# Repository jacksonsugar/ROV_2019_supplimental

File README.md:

# ROV_2019_supplimental
Documents and CAD for the 2019 ROV

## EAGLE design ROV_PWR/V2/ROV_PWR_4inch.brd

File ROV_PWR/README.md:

Two types here. The vicor product on the 4 inch failed and had to spec a new part. Never printed number 2.

Suggest making new one all together.

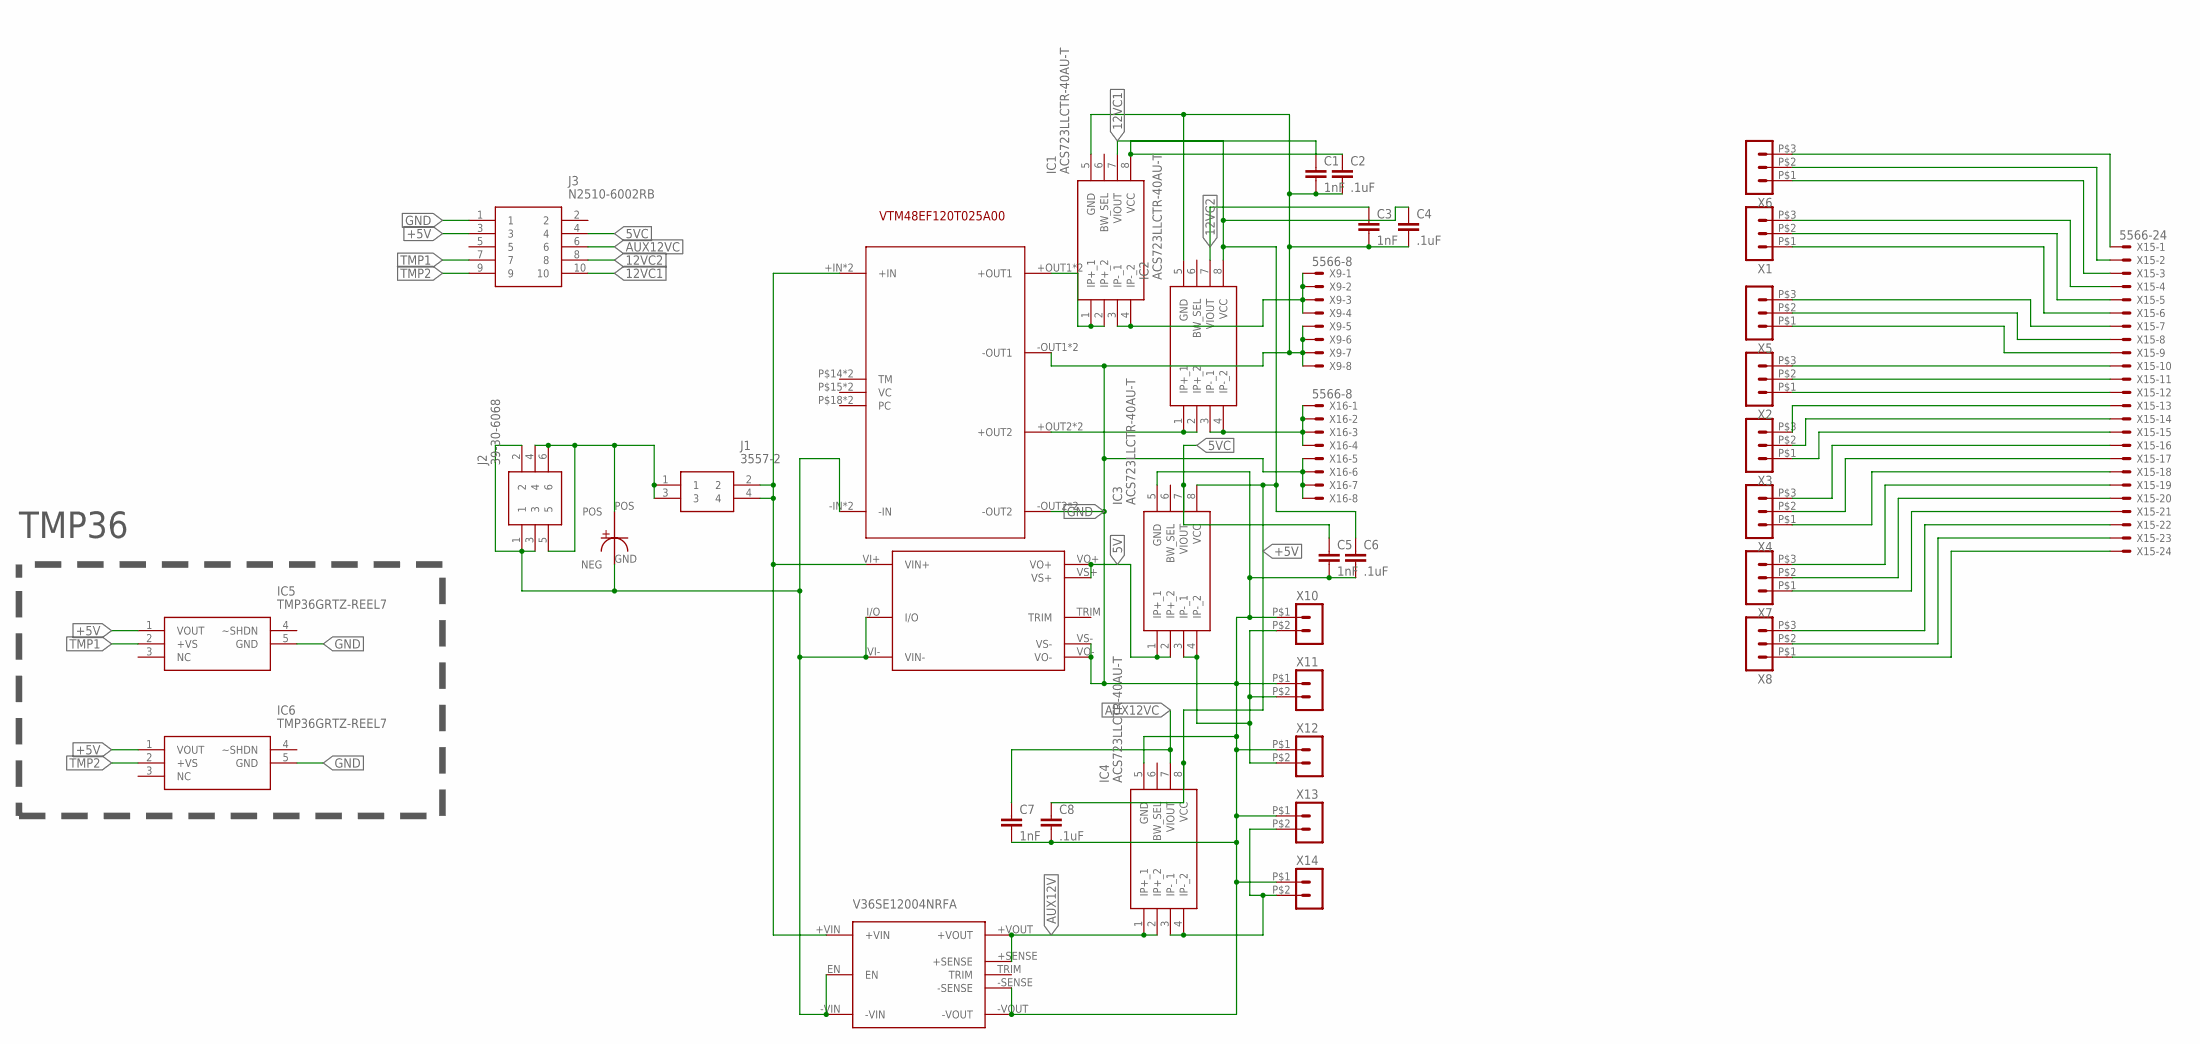
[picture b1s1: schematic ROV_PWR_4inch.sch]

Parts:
C1, C3, C5, C7: 1nF; C0402
C2, C4, C6, C8: .1uF; C0402
IC1, IC2, IC3, IC4: ACS723LLCTR-40AU-T; SOT127P600X175-8N
IC5, IC6: TMP36GRTZ-REEL7; SOT95P280X145-5N
J1: 3557-2
J2: 39-30-6068; 39306068
J3: N2510-6002RB; SHDR10W64P254_2X5_2002X859X100
U$1: VTM48EF120T025A00
U$2: KHHD006A0A41Z
U$3: V36SE12004NRFA
U$4: UBY1V222MHL
X1, X2, X3, X4, X5, X6, X7, X8: HEADER_POS3_43650-0315; 43650-0315
X9, X16: 5566-8
X10, X11, X12, X13, X14: HEADER_POS2_44914-0201; 44914-0201
X15: 5566-24

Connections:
5V: IC3.1 (IP+_1), IC3.2 (IP+_2), U$2.VO+, U$2.VS+
5VC: C5.1, IC3.7 (VIOUT), J3.4
12VC1: C1.1, IC1.7 (VIOUT), J3.10
12VC2: C3.1, IC2.7 (VIOUT), J3.8
+5V: C2.1, C4.1, C6.1, C8.1, IC1.8 (VCC), IC2.8 (VCC), IC3.8 (VCC), IC4.8 (VCC), IC5.1 (VOUT), IC6.1 (VOUT), J3.3
AUX12V: IC4.1 (IP+_1), IC4.2 (IP+_2), U$3.+SENSE, U$3.+VOUT
AUX12VC: C7.1, IC4.7 (VIOUT), J3.6
GND: C1.2, C2.2, C3.2, C4.2, C5.2, C6.2, C7.2, C8.2, IC1.5 (GND), IC2.5 (GND), IC3.5 (GND), IC4.5 (GND), IC5.5 (GND), IC6.5 (GND), J3.1, U$1.-OUT1, U$1.-OUT2, U$1.P$1 (-OUT1), U$1.P$4 (-OUT2), U$2.VO-, U$2.VS-, U$3.-SENSE, U$3.-VOUT, X9.5, X9.6, X9.7, X9.8, X10.P$1 (1), X11.P$1 (1), X12.P$1 (1), X13.P$1 (1), X14.P$1 (1), X16.5, X16.6, X16.7, X16.8
unnamed: X6.P$3 (3), X15.1
unnamed: X6.P$2 (2), X15.2
unnamed: X6.P$1 (1), X15.3
unnamed: X1.P$3 (3), X15.4
unnamed: X1.P$2 (2), X15.5
unnamed: X1.P$1 (1), X15.6
unnamed: X5.P$3 (3), X15.7
unnamed: X5.P$2 (2), X15.8
unnamed: X5.P$1 (1), X15.9
unnamed: X2.P$3 (3), X15.10
unnamed: X2.P$2 (2), X15.11
unnamed: X2.P$1 (1), X15.12
unnamed: X3.P$3 (3), X15.13
unnamed: X3.P$2 (2), X15.14
unnamed: X3.P$1 (1), X15.15
unnamed: X4.P$3 (3), X15.16
unnamed: X4.P$2 (2), X15.17
unnamed: X4.P$1 (1), X15.18
unnamed: X7.P$3 (3), X15.19
unnamed: X7.P$2 (2), X15.20
unnamed: X7.P$1 (1), X15.21
unnamed: X8.P$3 (3), X15.22
unnamed: X8.P$2 (2), X15.23
unnamed: X8.P$1 (1), X15.24
unnamed: J1.2, J1.4, U$1.+IN, U$1.P$9 (+IN), U$2.VI+ (VIN+), U$3.+VIN
unnamed: IC1.1 (IP+_1), IC1.2 (IP+_2), U$1.+OUT1, U$1.P$3 (+OUT1)
unnamed: J2.1, J2.2, J2.3, U$1.-IN, U$1.P$11 (-IN), U$2.I/O, U$2.VI- (VIN-), U$3.-VIN, U$3.EN, U$4.GND (NEG)
unnamed: J1.1, J1.3, J2.4, J2.5, J2.6, U$4.POS
unnamed: IC3.3 (IP-_1), IC3.4 (IP-_2), X10.P$2 (2), X11.P$2 (2), X12.P$2 (2)
unnamed: IC4.3 (IP-_1), IC4.4 (IP-_2), X13.P$2 (2), X14.P$2 (2)
unnamed: IC2.1 (IP+_1), IC2.2 (IP+_2), U$1.+OUT2, U$1.P$2 (+OUT2)
unnamed: IC2.3 (IP-_1), IC2.4 (IP-_2), X16.1, X16.2, X16.3, X16.4
unnamed: IC1.3 (IP-_1), IC1.4 (IP-_2), X9.1, X9.2, X9.3, X9.4
TMP1: IC5.2 (+VS), J3.7
TMP2: IC6.2 (+VS), J3.9

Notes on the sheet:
TMP36

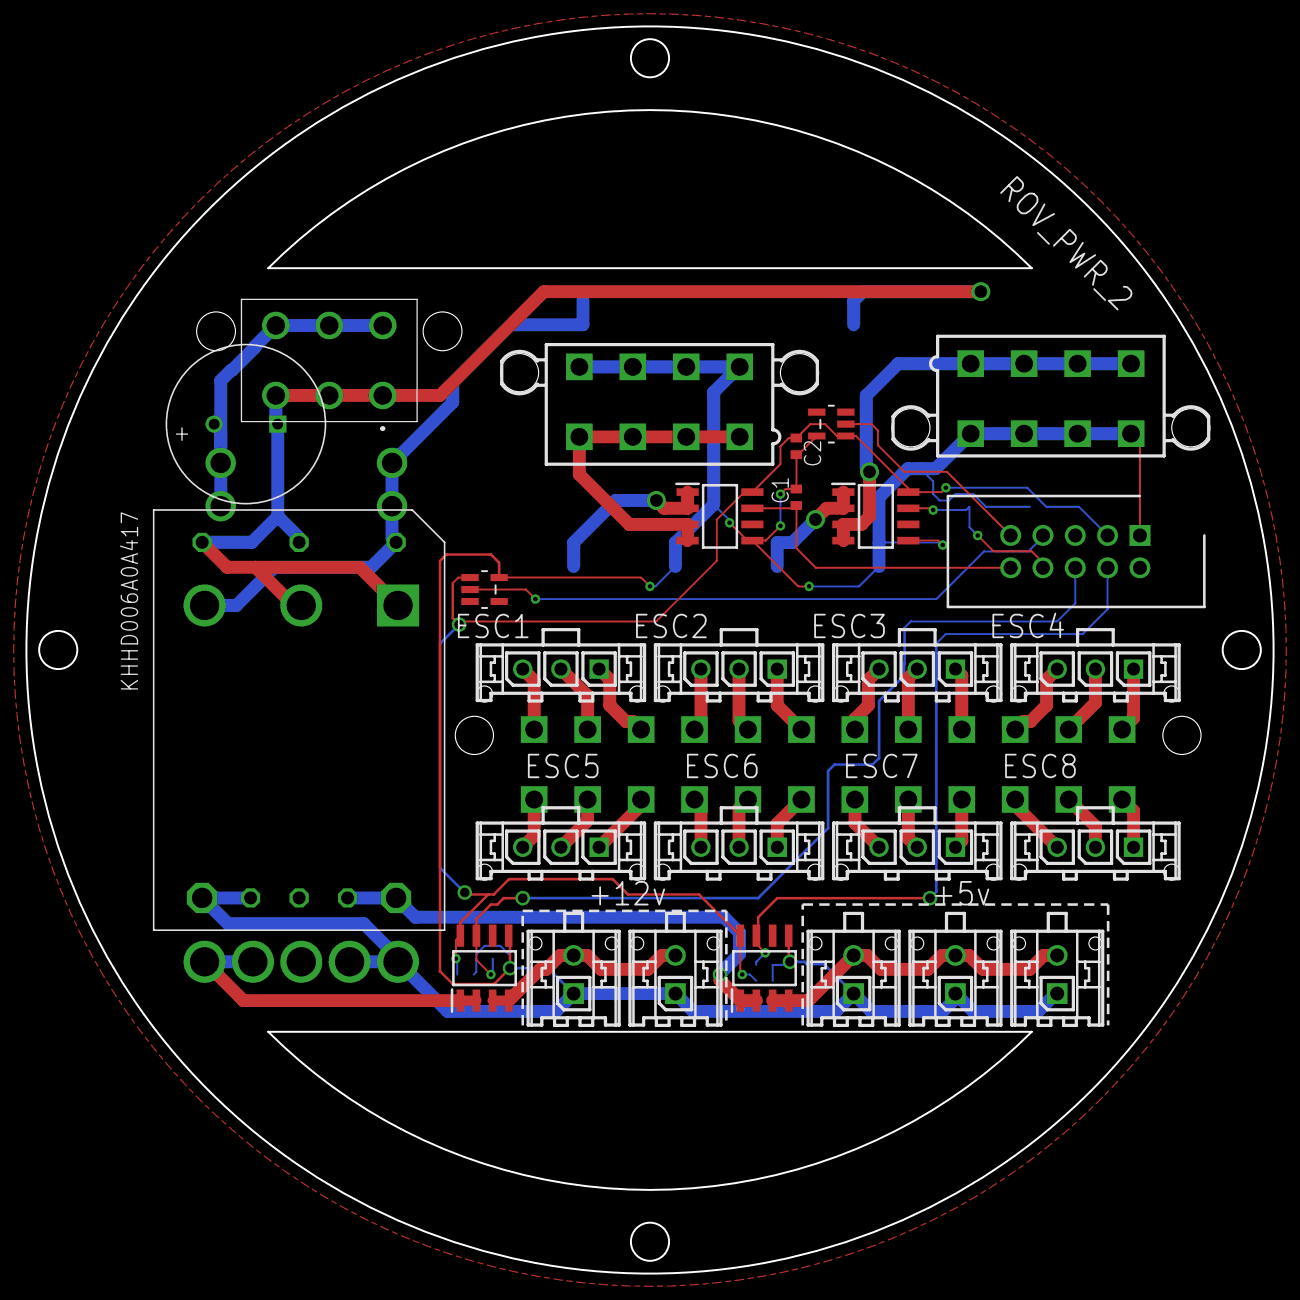
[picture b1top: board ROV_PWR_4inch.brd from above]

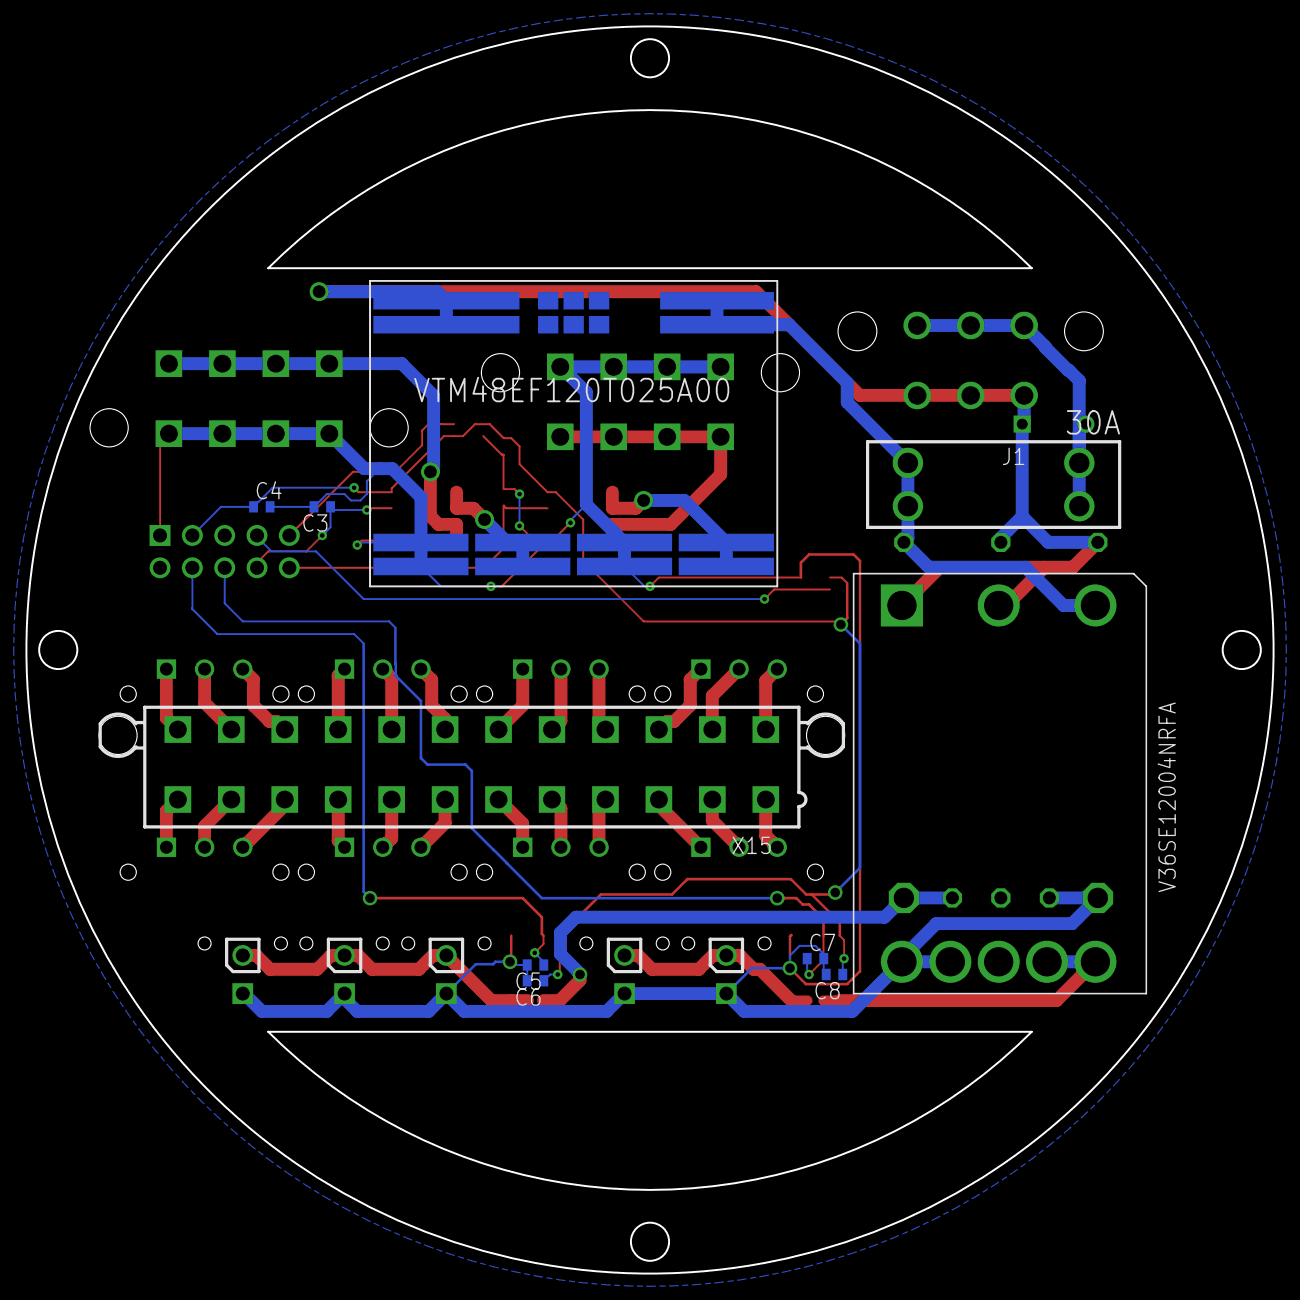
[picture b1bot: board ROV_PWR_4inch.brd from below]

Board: 2 copper layers, 98.0 x 98.0 mm, 37 parts (10 on the bottom side), 43 nets.

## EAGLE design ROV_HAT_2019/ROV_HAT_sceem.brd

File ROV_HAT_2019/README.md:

Designed for the NanoPi M4. Locatoin of the serial pins are propriatary.

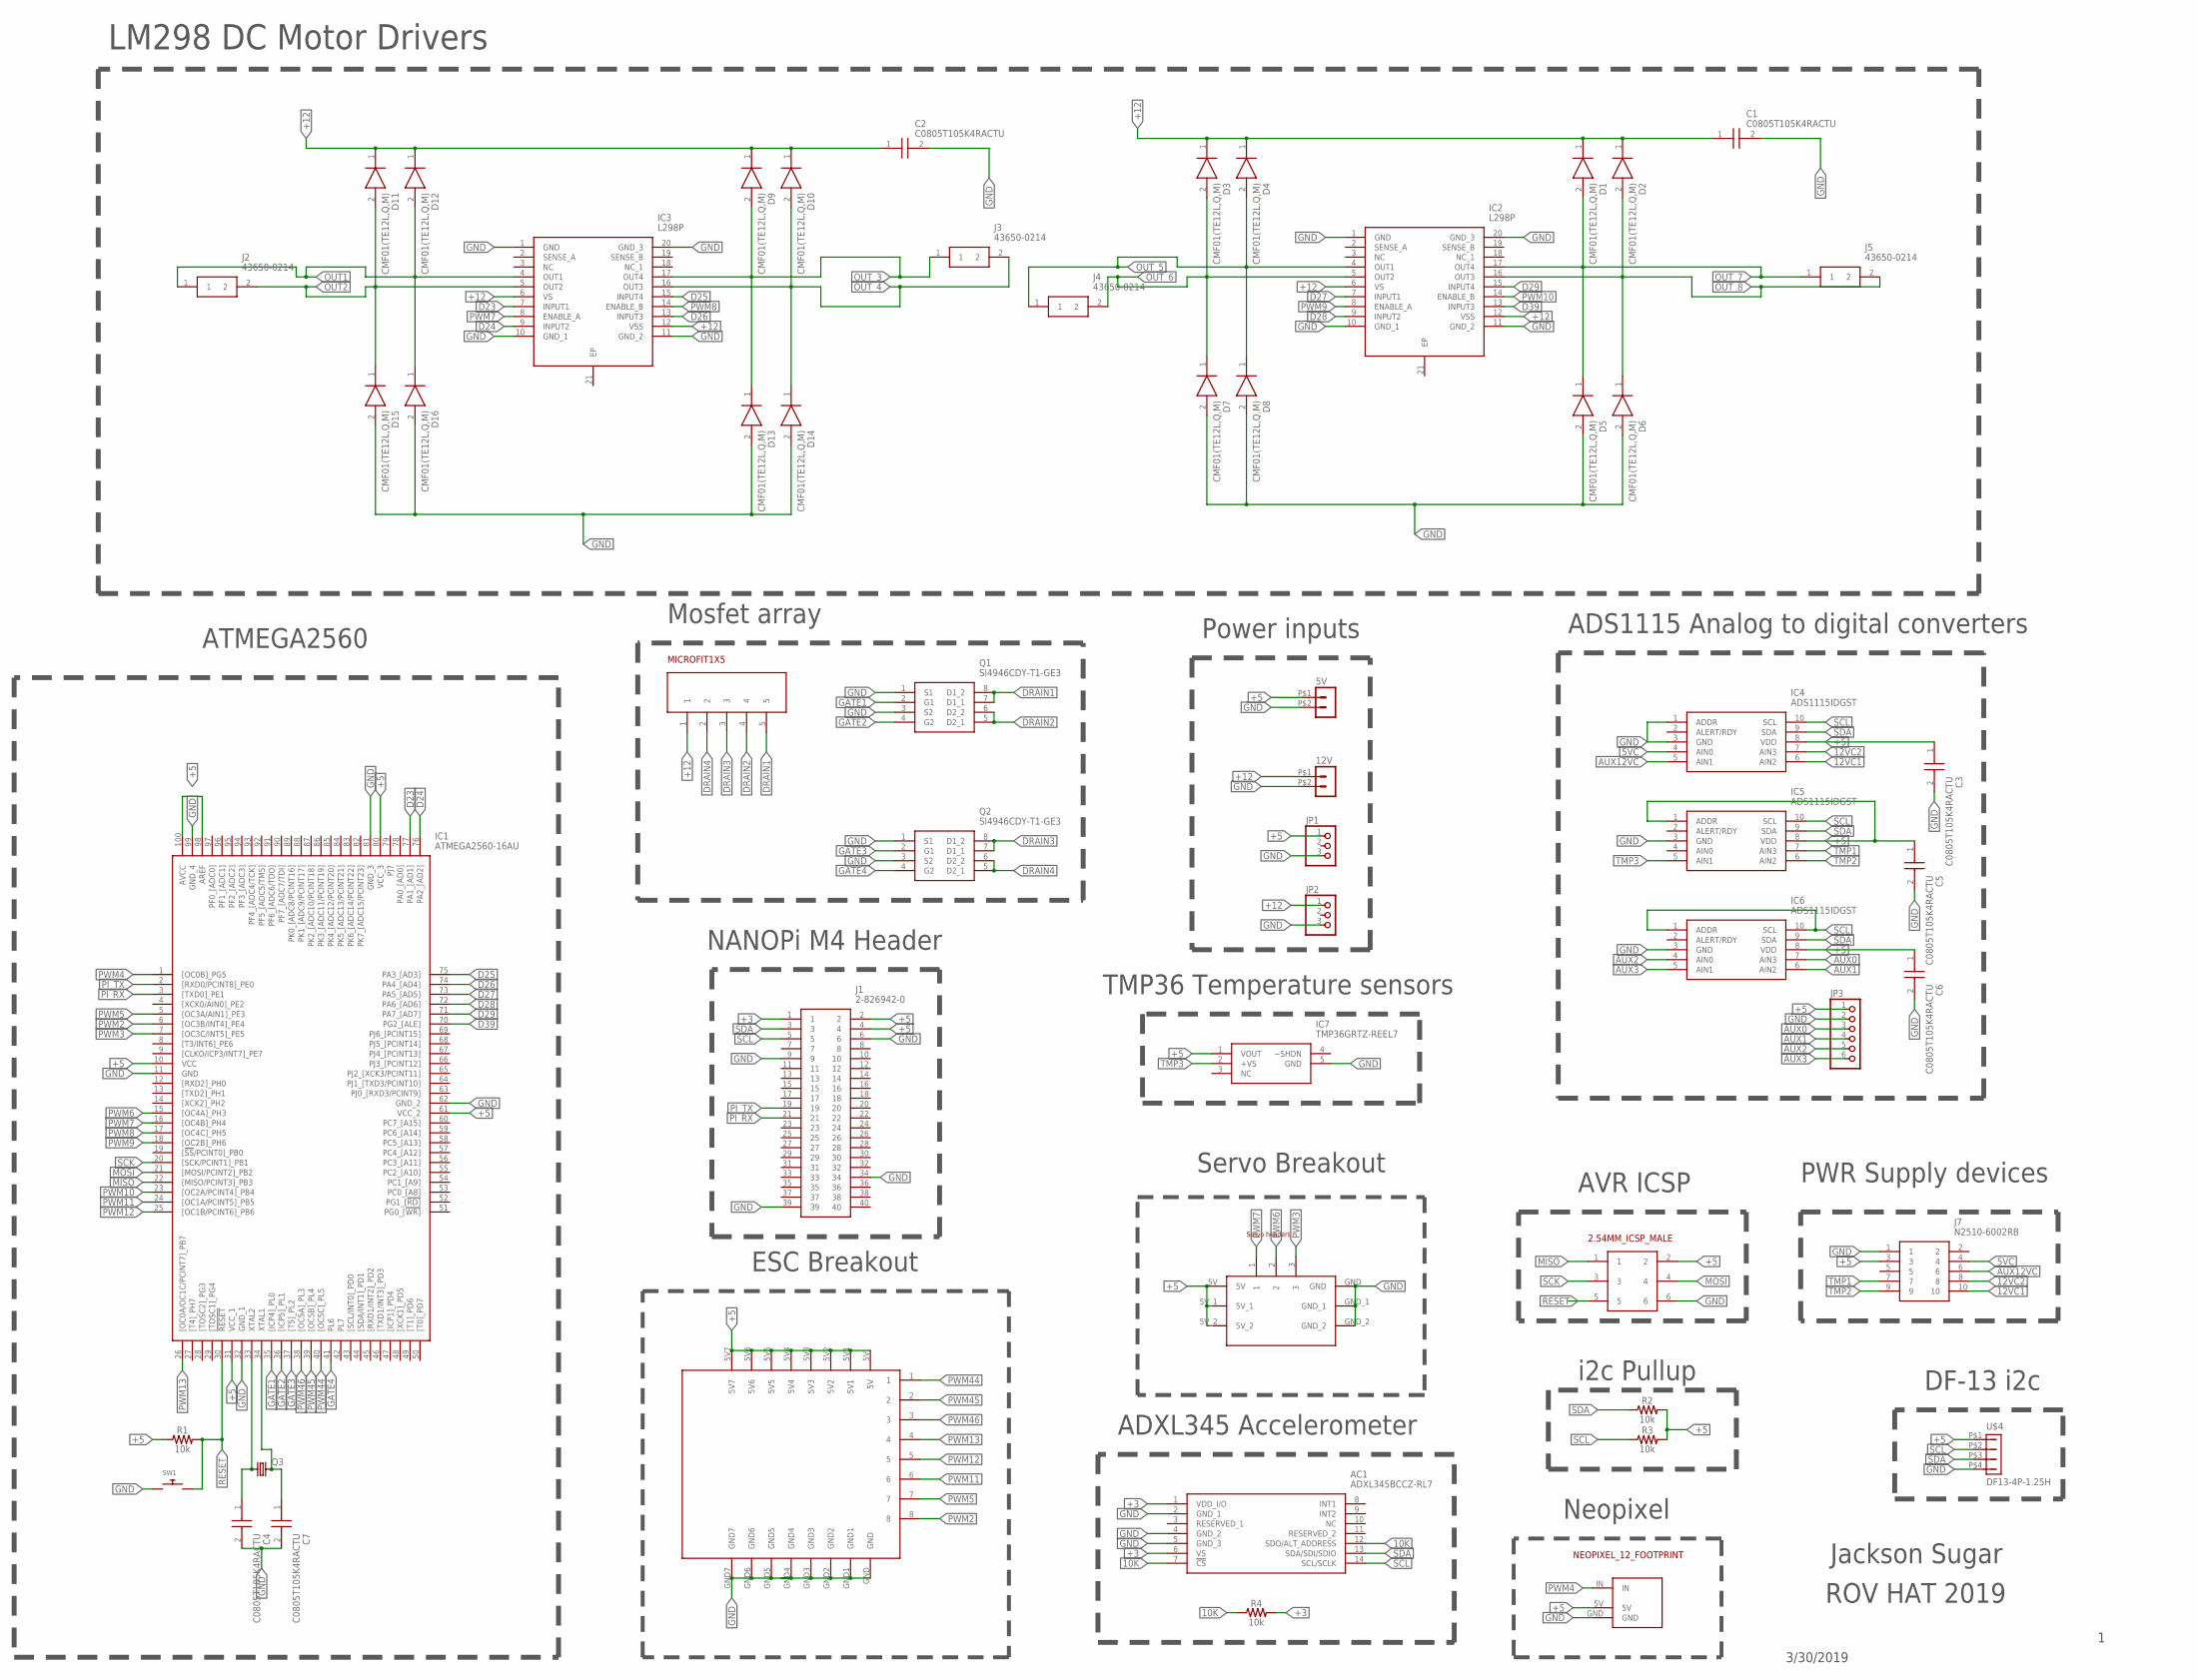
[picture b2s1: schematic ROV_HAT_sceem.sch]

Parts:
5V: HEADER_POS2_43045-0200; 43045-0200
12V: HEADER_POS2_43650-0200; 43650-0200
AC1: ADXL345BCCZ-RL7; CC-14-1
C1, C2, C3, C4, C5, C6, C7: C0805T105K4RACTU; CAPC2012X100N
D1, D2, D3, D4, D5, D6, D7, D8, D9, D10, D11, D12, D13, D14, D15, D16: CMF01(TE12L,Q,M); SODFL4724X108N
IC1: ATMEGA2560-16AU; QFP50P1600X1600X120-100N
IC2, IC3: L298P; SOIC127P1420X360-21N
IC4, IC5, IC6: ADS1115IDGST; SOP50P490X110-10N
IC7: TMP36GRTZ-REEL7; SOT95P280X145-5N
J1: 2-826942-0; HDRV40W63P254_2X20_5080X500X88
J2, J3, J4, J5: 43650-0214
J7: N2510-6002RB; SHDR10W64P254_2X5_2002X859X100
JP1, JP2: PINHD-1X3; 1X03
JP3: PINHD-1X6; 1X06
Q1, Q2: SI4946CDY-T1-GE3; SOIC127P600X175-8N
Q3: CRYSTALHC49S; HC49/S
R1, R2, R3, R4: 10k; 0603
SW1: SWITCH_PUSHBUTTONC&K_KSS; BTN_CK_KSS
U$1: 3X8_RIGHT_HEADER
U$2: 2.54MM_ICSP_MALE
U$3: NEOPIXEL_12_FOOTPRINT
U$4: DF13-4P-1.25H; DF13A-4P-1.25H
U$5: SERVO_PWM_HEADER
U$6: MICROFIT1X5

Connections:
5VC: IC4.4 (AIN0), J7.4
10K: AC1.7 (!CS), AC1.12 (SDO/ALT_ADDRESS), R4.1
12VC1: IC4.6 (AIN2), J7.10
12VC2: IC4.7 (AIN3), J7.8
+3: AC1.1 (VDD_I/O), AC1.6 (VS), J1.1, R4.2
+5: 5V.P$1 (1), C3.1, C5.1, C6.1, IC1.10 (VCC), IC1.31 (VCC_1), IC1.61 (VCC_2), IC1.80 (VCC_3), IC1.98 (AREF), IC1.100 (AVCC), IC4.8 (VDD), IC5.1 (ADDR), IC5.8 (VDD), IC6.8 (VDD), IC7.1 (VOUT), J1.2, J1.4, J7.3, JP1.1, JP3.1, R1.1, R2.2, R3.2, U$1.5V, U$1.5V1, U$1.5V2, U$1.5V3, U$1.5V4, U$1.5V5, U$1.5V6, U$1.5V7, U$2.2, U$3.5V, U$4.P$1 (1), U$5.5V, U$5.5V_1, U$5.5V_2
+12: 12V.P$1 (1), C1.1, C2.1, D1.1 (K), D2.1 (K), D3.1 (K), D4.1 (K), D9.1 (K), D10.1 (K), D11.1 (K), D12.1 (K), IC2.6 (VS), IC2.12 (VSS), IC3.6 (VS), IC3.12 (VSS), JP2.1, U$6.1
AUX0: IC6.7 (AIN3), JP3.3
AUX1: IC6.6 (AIN2), JP3.4
AUX2: IC6.4 (AIN0), JP3.5
AUX3: IC6.5 (AIN1), JP3.6
AUX12VC: IC4.5 (AIN1), J7.6
D23: IC1.77 (PA1_[AD1]), IC3.7 (INPUT1)
D24: IC1.76 (PA2_[AD2]), IC3.9 (INPUT2)
D25: IC1.75 (PA3_[AD3]), IC3.15 (INPUT4)
D26: IC1.74 (PA4_[AD4]), IC3.13 (INPUT3)
D27: IC1.73 (PA5_[AD5]), IC2.7 (INPUT1)
D28: IC1.72 (PA6_[AD6]), IC2.9 (INPUT2)
D29: IC1.71 (PA7_[AD7]), IC2.15 (INPUT4)
D39: IC1.70 (PG2_[ALE]), IC2.13 (INPUT3)
DRAIN1: Q1.7 (D1_1), Q1.8 (D1_2), U$6.5
DRAIN2: Q1.5 (D2_1), Q1.6 (D2_2), U$6.4
DRAIN3: Q2.7 (D1_1), Q2.8 (D1_2), U$6.3
DRAIN4: Q2.5 (D2_1), Q2.6 (D2_2), U$6.2
GATE1: IC1.35 ([ICP4]_PL0), Q1.2 (G1)
GATE2: IC1.36 ([ICP5]_PL1), Q1.4 (G2)
GATE3: IC1.37 ([T5]_PL2), Q2.2 (G1)
GATE4: IC1.41 (PL6), Q2.4 (G2)
GND: 5V.P$2 (2), 12V.P$2 (2), AC1.2 (GND_1), AC1.4 (GND_2), AC1.5 (GND_3), C1.2, C2.2, C3.2, C4.2, C5.2, C6.2, C7.2, D5.2 (A), D6.2 (A), D7.2 (A), D8.2 (A), D13.2 (A), D14.2 (A), D15.2 (A), D16.2 (A), IC1.11 (GND), IC1.32 (GND_1), IC1.62 (GND_2), IC1.81 (GND_3), IC1.99 (GND_4), IC2.1 (GND), IC2.10 (GND_1), IC2.11 (GND_2), IC2.20 (GND_3), IC3.1 (GND), IC3.10 (GND_1), IC3.11 (GND_2), IC3.20 (GND_3), IC4.1 (ADDR), IC4.3 (GND), IC5.3 (GND), IC6.3 (GND), IC7.5 (GND), J1.6, J1.9, J1.34, J1.39, J7.1, JP1.3, JP2.3, JP3.2, Q1.1 (S1), Q1.3 (S2), Q2.1 (S1), Q2.3 (S2), SW1.P$1, U$1.GND, U$1.GND1, U$1.GND2, U$1.GND3, U$1.GND4, U$1.GND5, U$1.GND6, U$1.GND7, U$2.6, U$3.GND, U$4.P$4 (4), U$5.GND, U$5.GND_1, U$5.GND_2
MISO: IC1.22 ([MISO/PCINT3]_PB3), U$2.1
MOSI: IC1.21 ([MOSI/PCINT2]_PB2), U$2.4
unnamed: C4.1, IC1.33 (XTAL2), Q3.1
unnamed: C7.1, IC1.34 (XTAL1), Q3.2
OUT1: D12.2 (A), D16.1 (K), IC3.4 (OUT1), J2.1
OUT2: D11.2 (A), D15.1 (K), IC3.5 (OUT2), J2.2
OUT_3: D9.2 (A), D13.1 (K), IC3.17 (OUT4), J3.1
OUT_4: D10.2 (A), D14.1 (K), IC3.16 (OUT3), J3.2
OUT_5: D4.2 (A), D8.1 (K), IC2.4 (OUT1), J4.1
OUT_6: D3.2 (A), D7.1 (K), IC2.5 (OUT2), J4.2
OUT_7: D1.2 (A), D5.1 (K), IC2.17 (OUT4), J5.1
OUT_8: D2.2 (A), D6.1 (K), IC2.16 (OUT3), J5.2
PI_RX: IC1.3 ([TXD0]_PE1), J1.21
PI_TX: IC1.2 ([RXD0/PCINT8]_PE0), J1.19
PWM2: IC1.6 ([OC3B/INT4]_PE4), U$1.8
PWM3: IC1.7 ([OC3C/INT5]_PE5), U$5.3
PWM4: IC1.1 ([OC0B]_PG5), U$3.IN
PWM5: IC1.5 ([OC3A/AIN1]_PE3), U$1.7
PWM6: IC1.15 ([OC4A]_PH3), U$5.2
PWM7: IC1.16 ([OC4B]_PH4), IC3.8 (ENABLE_A), U$5.1
PWM8: IC1.17 ([OC4C]_PH5), IC3.14 (ENABLE_B)
PWM9: IC1.18 ([OC2B]_PH6), IC2.8 (ENABLE_A)
PWM10: IC1.23 ([OC2A/PCINT4]_PB4), IC2.14 (ENABLE_B)
PWM11: IC1.24 ([OC1A/PCINT5]_PB5), U$1.6
PWM12: IC1.25 ([OC1B/PCINT6]_PB6), U$1.5
PWM13: IC1.26 ([OC0A/OC1C/PCINT7]_PB7), U$1.4
PWM44: IC1.40 ([OC5C]_PL5), U$1.1
PWM45: IC1.39 ([OC5B]_PL4), U$1.2
PWM46: IC1.38 ([OC5A]_PL3), U$1.3
RESET: IC1.30 (!RESET), R1.2, SW1.P$2, U$2.5
SCK: IC1.20 ([SCK/PCINT1]_PB1), U$2.3
SCL: AC1.14 (SCL/SCLK), IC4.10 (SCL), IC5.10 (SCL), IC6.1 (ADDR), IC6.10 (SCL), J1.5, R3.1, U$4.P$2 (2)
SDA: AC1.13 (SDA/SDI/SDIO), IC4.9 (SDA), IC5.9 (SDA), IC6.9 (SDA), J1.3, R2.1, U$4.P$3 (3)
TMP1: IC5.7 (AIN3), J7.7
TMP2: IC5.6 (AIN2), J7.9
TMP3: IC5.5 (AIN1), IC7.2 (+VS)

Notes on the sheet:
LM298 DC Motor Drivers
ADS1115 Analog to digital converters
TMP36 Temperature sensors
PWR Supply devices
Mosfet array
ADXL345 Accelerometer
NANOPi M4 Header
Power inputs
AVR ICSP
i2c Pullup
DF-13 i2c
ATMEGA2560
Neopixel
ESC Breakout
Servo Breakout
Jackson Sugar
ROV HAT 2019
3/30/2019

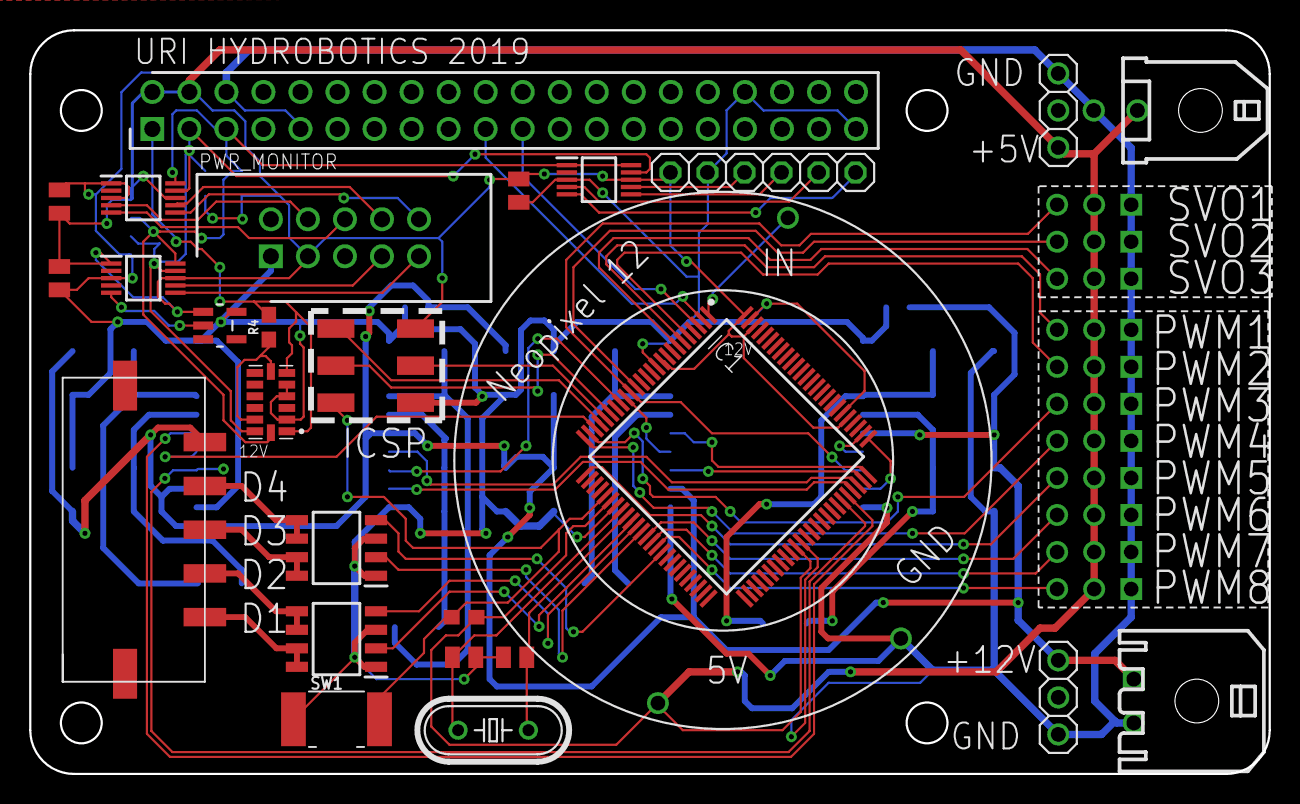
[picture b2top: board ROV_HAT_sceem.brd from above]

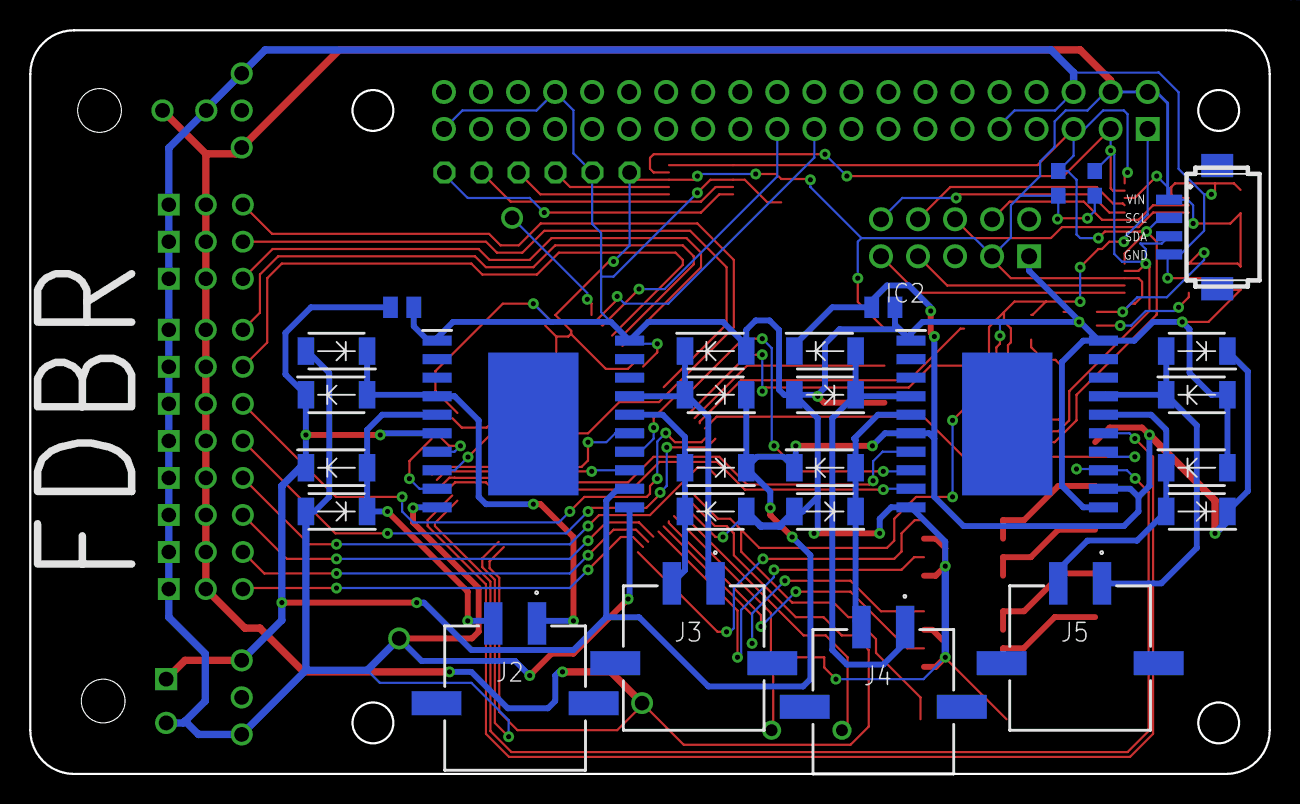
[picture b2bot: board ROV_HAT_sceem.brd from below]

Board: 2 copper layers, 85.0 x 51.0 mm, 56 parts (27 on the bottom side), 65 nets.

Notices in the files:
parts and their libraries:
SparkFun-Resistors: Licensing: Creative Commons ShareAlike 4.0 International - https://creativecommons.org/licenses/by-sa/4.0
